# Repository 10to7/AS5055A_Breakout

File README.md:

AS5055A_Breakout
================

AS5055A hall effect encoder breakout board.

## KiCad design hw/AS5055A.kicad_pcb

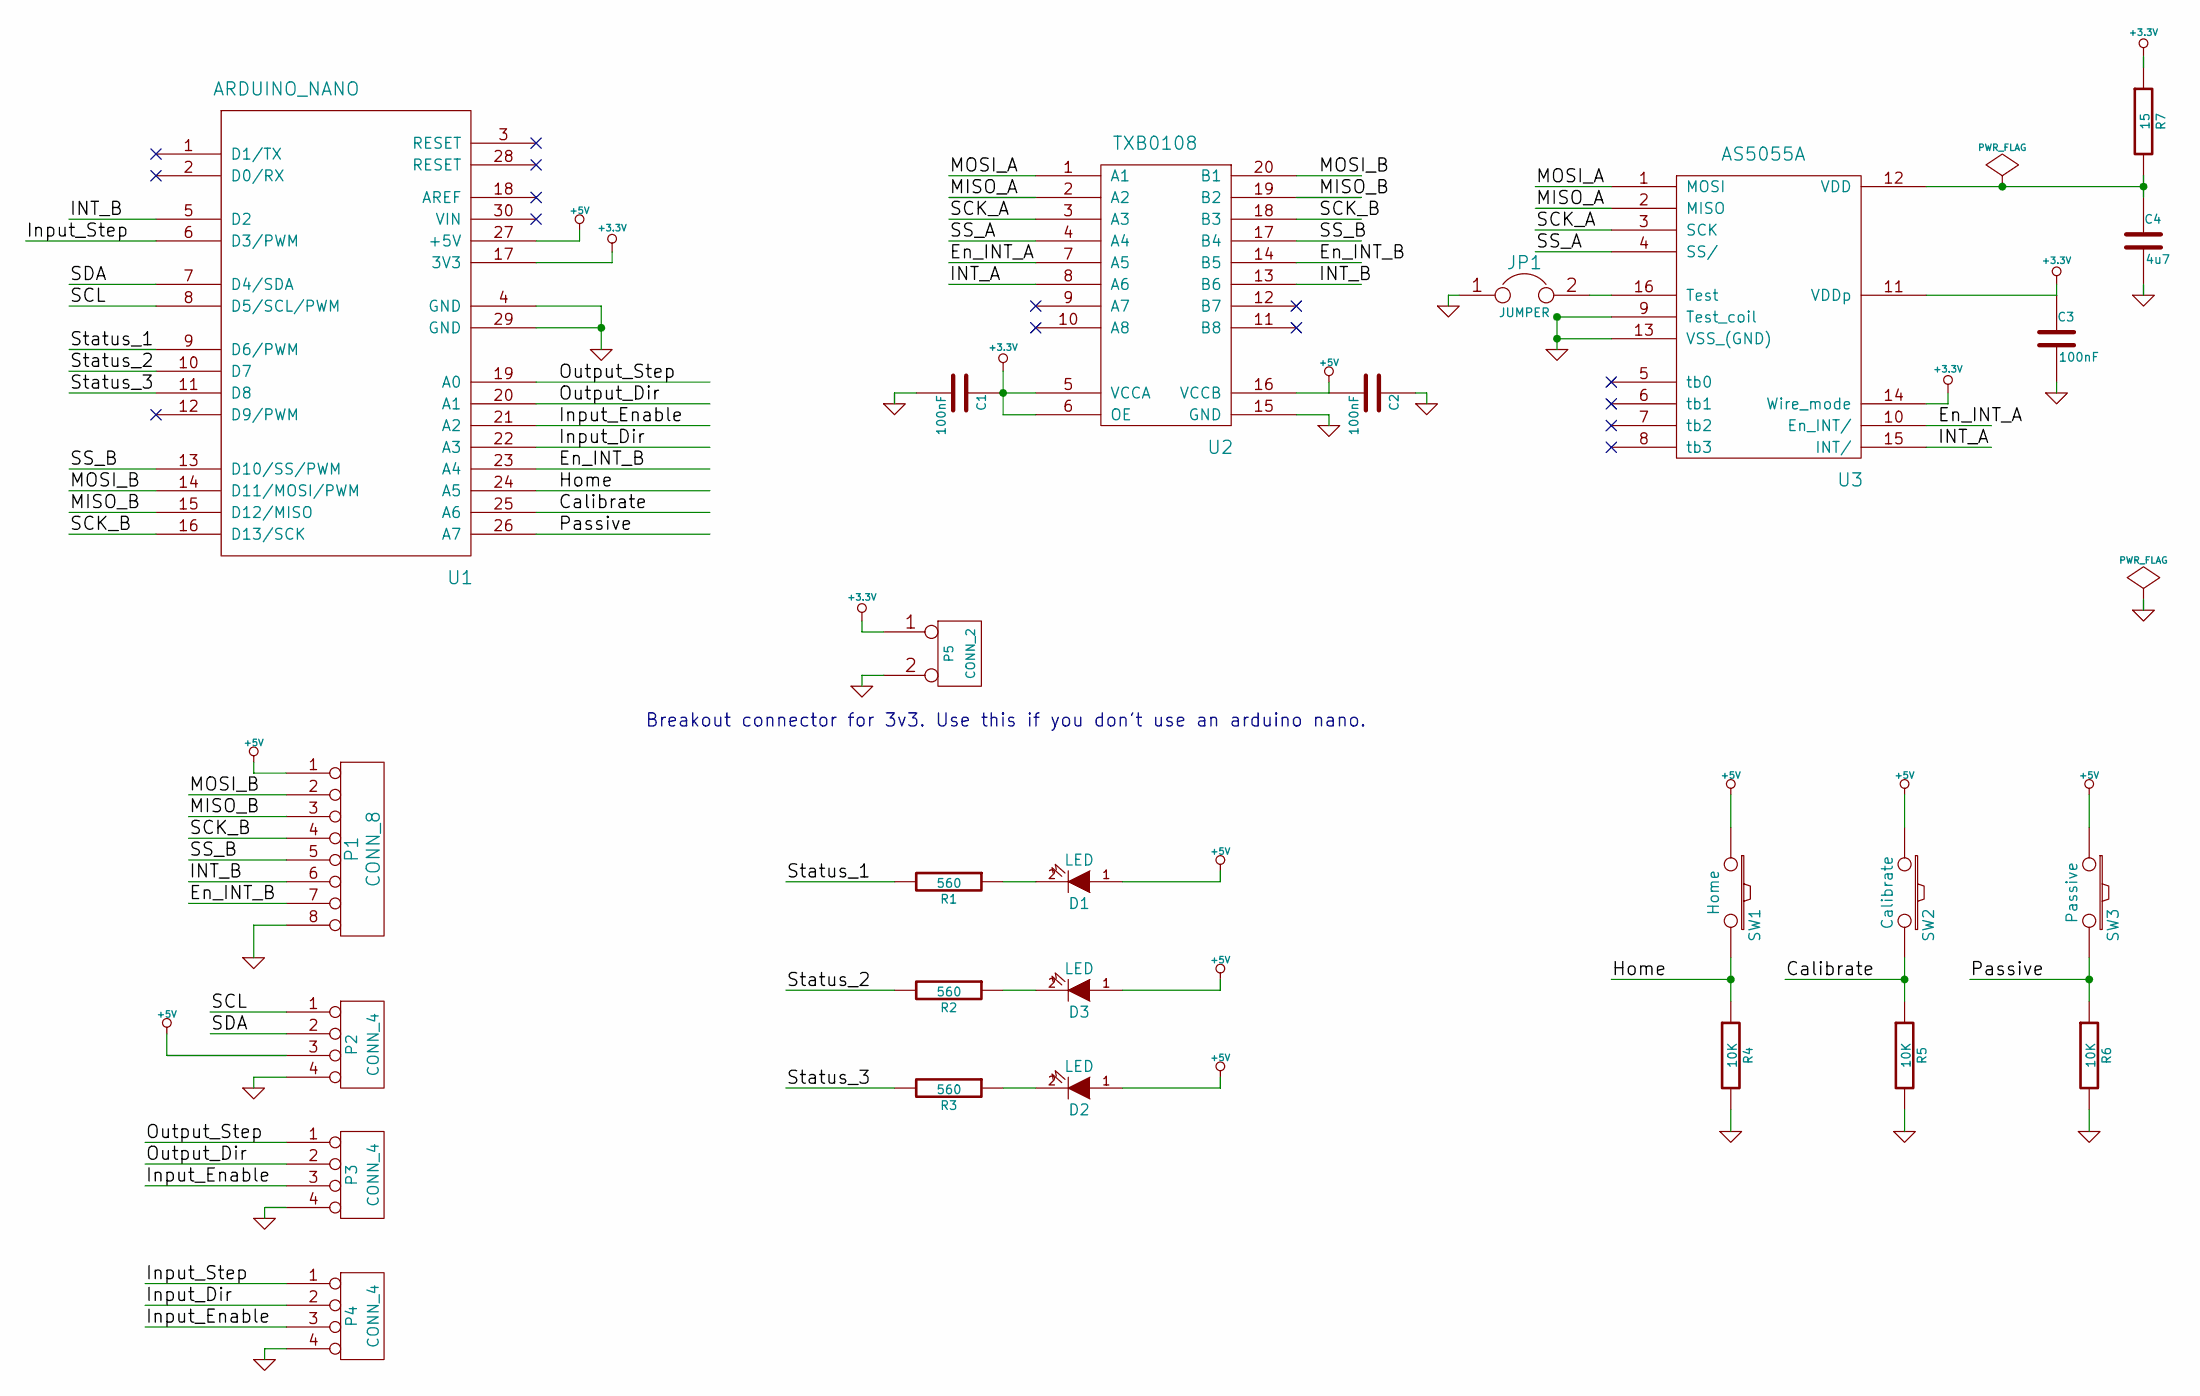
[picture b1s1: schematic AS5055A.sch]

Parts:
C1, C2, C3: 100nF
C4: 4u7
D1, D2, D3: LED
JP1: JUMPER
P1: CONN_8
P2, P3, P4: CONN_4
P5: CONN_2
R1, R2, R3: 560
R4, R5, R6: 10K
R7: 15
SW1: Home
SW2: Calibrate
SW3: Passive
U1: ARDUINO_NANO
U2: TXB0108
U3: AS5055A

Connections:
+3.3V: C1.1, C3.1, P5.1, R7.1, U1.17 (3V3), U2.5 (VCCA), U2.6 (OE), U3.11 (VDDp), U3.14 (Wire_mode)
+5V: C2.2, D1.1 (A), D2.1 (A), D3.1 (A), P1.1, P2.3, SW1.1, SW2.1, SW3.1, U1.27 (+5V), U2.16 (VCCB)
/Calibrate: R5.1, SW2.2, U1.25 (A6)
/En_INT_A: U2.7 (A5), U3.10 (En_INT/)
/En_INT_B: P1.7, U1.23 (A4), U2.14 (B5)
/Home: R4.1, SW1.2, U1.24 (A5)
/INT_A: U2.8 (A6), U3.15 (INT/)
/INT_B: P1.6, U1.5 (D2), U2.13 (B6)
/Input_Dir: P4.2, U1.22 (A3)
/Input_Enable: P3.3, P4.3, U1.21 (A2)
/Input_Step: P4.1, U1.6 (D3/PWM)
/MISO_A: U2.2 (A2), U3.2 (MISO)
/MISO_B: P1.3, U1.15 (D12/MISO), U2.19 (B2)
/MOSI_A: U2.1 (A1), U3.1 (MOSI)
/MOSI_B: P1.2, U1.14 (D11/MOSI/PWM), U2.20 (B1)
/Output_Dir: P3.2, U1.20 (A1)
/Output_Step: P3.1, U1.19 (A0)
/Passive: R6.1, SW3.2, U1.26 (A7)
/SCK_A: U2.3 (A3), U3.3 (SCK)
/SCK_B: P1.4, U1.16 (D13/SCK), U2.18 (B3)
/SCL: P2.1, U1.8 (D5/SCL/PWM)
/SDA: P2.2, U1.7 (D4/SDA)
/SS_A: U2.4 (A4), U3.4 (SS/)
/SS_B: P1.5, U1.13 (D10/SS/PWM), U2.17 (B4)
/Status_1: R1.2, U1.9 (D6/PWM)
/Status_2: R2.2, U1.10 (D7)
/Status_3: R3.2, U1.11 (D8)
GND: C1.2, C2.1, C3.2, C4.2, JP1.1, P1.8, P2.4, P3.4, P4.4, P5.2 (PM), R4.2, R5.2, R6.2, U1.4 (GND), U1.29 (GND), U2.15 (GND), U3.9 (Test_coil), U3.13 (VSS_(GND))
unnamed: C4.1, R7.2, U3.12 (VDD)
unnamed: D1.2 (K), R1.1
unnamed: D2.2 (K), R3.1
unnamed: D3.2 (K), R2.1
unnamed: JP1.2, U3.16 (Test)

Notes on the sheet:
Breakout connector for 3v3. Use this if you don't use an arduino nano.

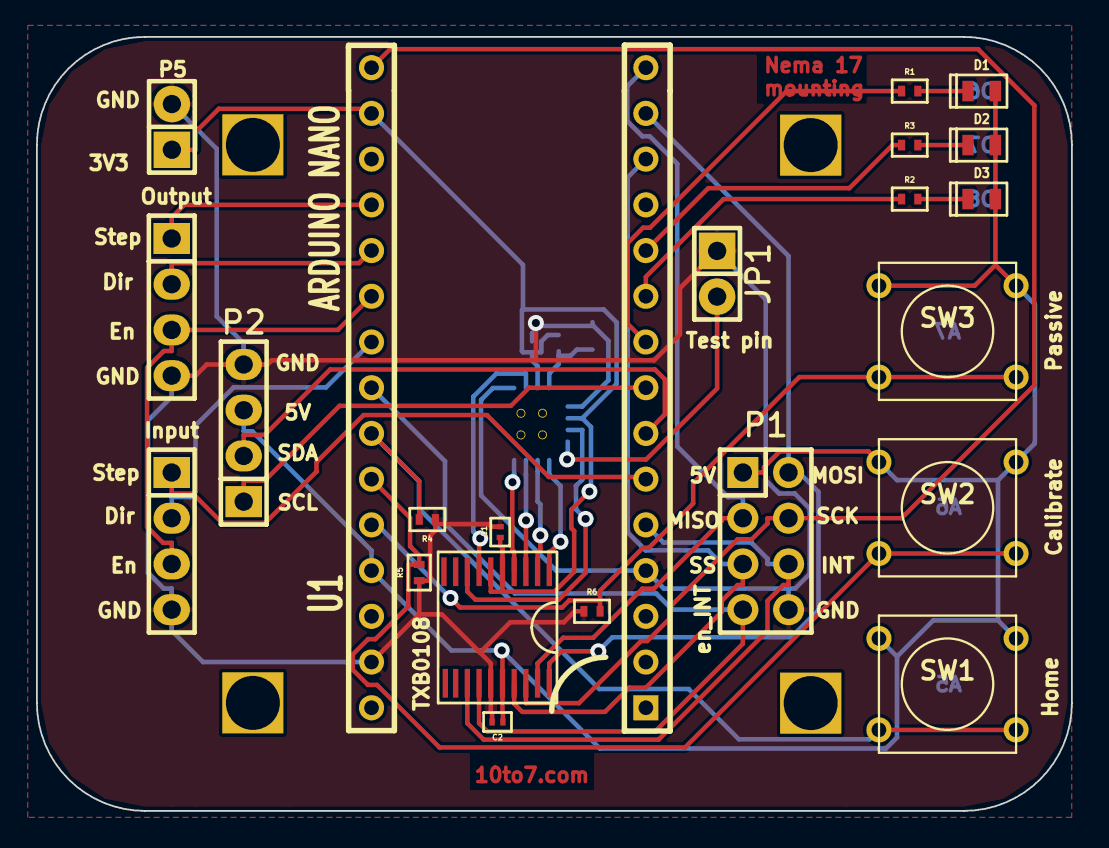
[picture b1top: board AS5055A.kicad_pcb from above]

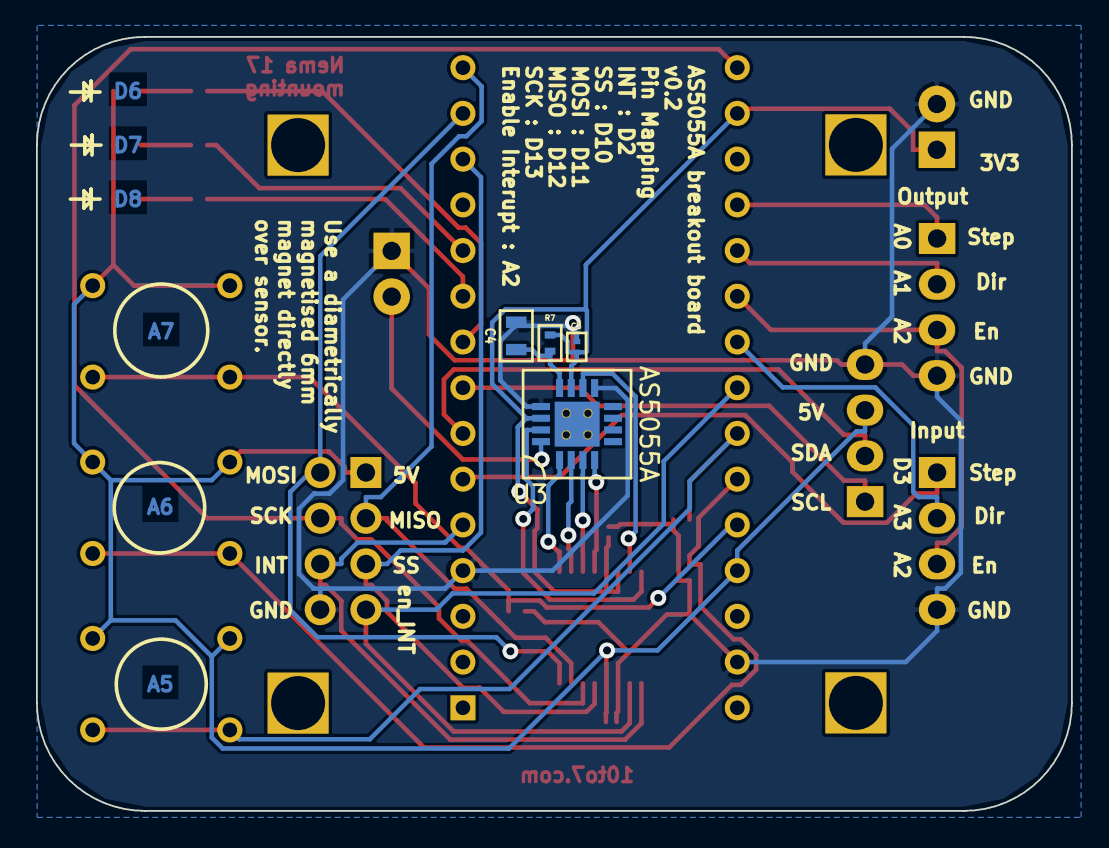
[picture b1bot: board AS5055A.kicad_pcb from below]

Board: 2 copper layers, 57.5 x 43.0 mm, 30 parts (4 on the bottom side), 33 nets.

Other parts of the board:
3mmHole_1, 3mmHole_2, 3mmHole_3, 3mmHole_4: VAL**; 3mmHole

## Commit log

2014-05-30 first revision of the encoder board
2014-06-01 Fixed some text consistency issues with the silk mask.
2014-06-04 Updated with revised arduino nano footprint
